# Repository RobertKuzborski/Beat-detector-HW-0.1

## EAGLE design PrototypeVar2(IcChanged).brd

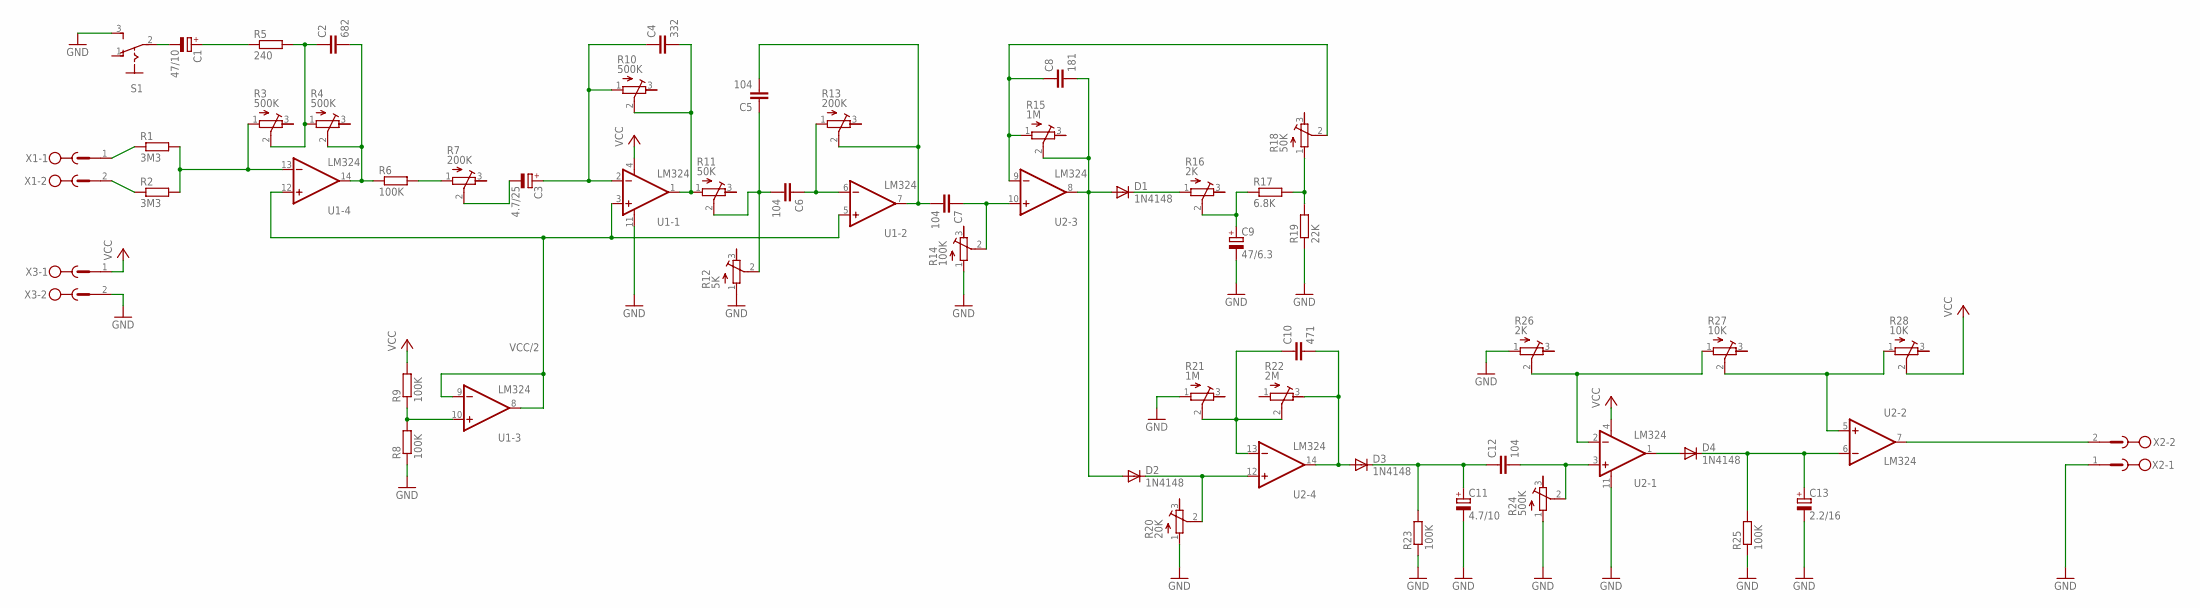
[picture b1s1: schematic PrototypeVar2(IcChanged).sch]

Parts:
C1: 47/10; E2,5-7
C2: 682; C050-035X075
C3: 4.7/25; E2,5-7
C4: 332; C050-035X075
C5, C6, C7, C12: 104; C050-035X075
C8: 181; C050-035X075
C9: 47/6.3; E2,5-7
C10: 471; C050-035X075
C11: 4.7/10; E2,5-7
C13: 2.2/16; E2,5-7
D1, D2, D3, D4: 1N4148; DO35-10
R1, R2: 3M3; 0204/7
R3, R4, R10, R24: 500K; RTRIM64W
R5: 240; 0204/7
R6, R23, R25: 100K; 0204/7
R7, R13: 200K; RTRIM64W
R8, R9: 100K; 0207/10
R11, R18: 50K; RTRIM64W
R12: 5K; RTRIM64W
R14: 100K; RTRIM64W
R15, R21: 1M; RTRIM64W
R16, R26: 2K; RTRIM64W
R17: 6.8K; 0204/7
R19: 22K; 0204/7
R20: 20K; RTRIM64W
R22: 2M; RTRIM64W
R27, R28: 10K; RTRIM64W
S1: 255SB
U1-, U2-: LM324; SOIC-14
X1, X2, X3: MSTBV2

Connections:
GND: C9.-, C11.-, C13.-, R8.1, R12.1 (A), R14.1 (A), R19.1, R20.1 (A), R21.1 (A), R23.1, R24.1 (A), R25.1, R26.1 (A), S1.3 (S), U1-.11 (V-), U2-.11 (V-), X2.1, X3.2
unnamed: C3.+, C4.1, R10.1 (A), U1-.2 (-IN)
unnamed: C4.2, R10.2 (S), R11.1 (A), U1-.1 (OUT)
unnamed: C5.1, C6.2, R11.2 (S), R12.2 (S)
unnamed: C5.2, C7.2, R13.2 (S), U1-.7 (OUT)
unnamed: C7.1, R14.2 (S), U2-.10 (+IN)
unnamed: C6.1, R13.1 (A), U1-.6 (-IN)
unnamed: C8.1, R15.1 (A), R18.2 (S), U2-.9 (-IN)
unnamed: D1.C, R16.1 (A)
unnamed: C1.+, R5.1
unnamed: C9.+, R16.2 (S), R17.1
unnamed: C2.2, R4.2 (S), R6.1, U1-.14 (OUT)
unnamed: D2.C, R20.2 (S), U2-.12 (+IN)
unnamed: C10.1, R21.2 (S), R22.2 (S), U2-.13 (-IN)
unnamed: C2.1, R3.2 (S), R4.1 (A), R5.2
unnamed: C10.2, D3.A, R22.3 (E), U2-.14 (OUT)
unnamed: C11.+, C12.1, D3.C, R23.2
unnamed: C12.2, R24.2 (S), U2-.3 (+IN)
unnamed: D4.A, U2-.1 (OUT)
unnamed: C13.+, D4.C, R25.2, U2-.6 (-IN)
unnamed: R26.2 (S), R27.1 (A), U2-.2 (-IN)
unnamed: R27.2 (S), R28.1 (A), U2-.5 (+IN)
unnamed: R1.1, X1.1
unnamed: R17.2, R18.1 (A), R19.2
unnamed: R8.2, R9.1, U1-.10 (+IN)
unnamed: R6.2, R7.1 (A)
unnamed: C3.-, R7.2 (S)
unnamed: U2-.7 (OUT), X2.2
unnamed: C1.-, S1.2
unnamed: R1.2, R2.2, R3.1 (A), U1-.13 (-IN)
unnamed: R2.1, X1.2
U2-: C8.2, D1.A, D2.A, R15.2 (S), U2-.8 (OUT)
VCC: R9.2, R28.2 (S), U1-.4 (V+), U2-.4 (V+), X3.1
VCC/2: U1-.3 (+IN), U1-.5 (+IN), U1-.8 (OUT), U1-.9 (-IN), U1-.12 (+IN)

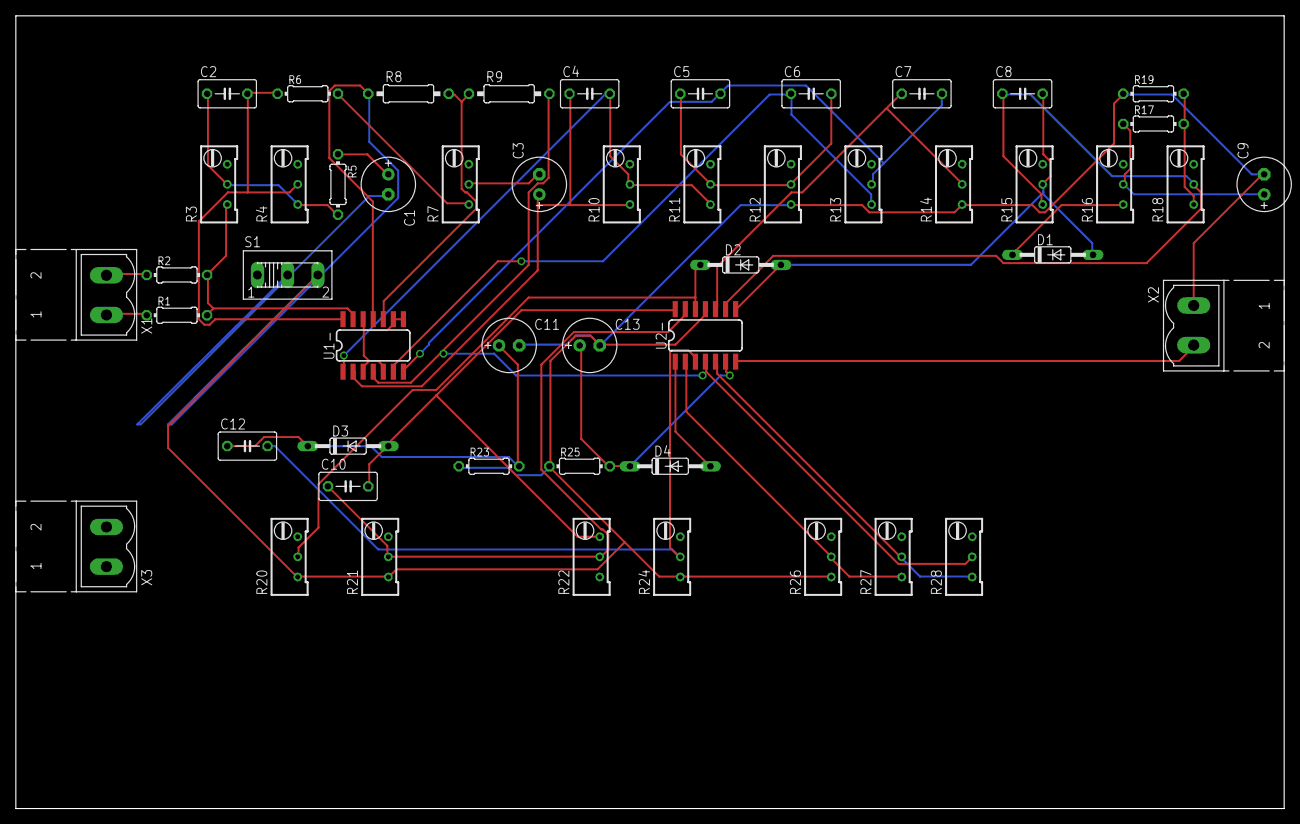
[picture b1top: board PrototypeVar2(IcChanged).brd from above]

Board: 2 copper layers, 160.0 x 100.0 mm, 51 parts (0 on the bottom side), 34 nets.
